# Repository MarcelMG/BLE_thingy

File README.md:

# BLEthingy
BLEthingy is a small battery-powered device with Bluetooth-Low-Energy connectivity.

The main microcontroller used is an AVR ATtiny3216 from the new tiny-1 series.

BLE connectivity is provided by a RN4871-I RF module.

There is an ADXL345 3-axis accelerometer onboard for motion detection. It sits on a GY-291 breakout-board, which is very cheap and avoids hand-soldering the tiny package of the ADXL345 which is virtually impossible without hot air / reflow oven. The GY-291 has to be slightly modified, see [here](https://github.com/MarcelMG/BLE_thingy/blob/master/hardware/GY-291_mod.md) for further instructions.

A pushbutton and a user LED are also onboard.

On the back of the PCB, a holder for a CR2032 coin cell is mounted.

An enclosure has been designed which can be 3D-printed.

(c) 2019 Marcel Meyer-Garcia
<br />This work (hardware and software) is licensed under a <a rel="license" href="http://creativecommons.org/licenses/by-nc/4.0/">Creative Commons Attribution-NonCommercial 4.0 International License</a>.

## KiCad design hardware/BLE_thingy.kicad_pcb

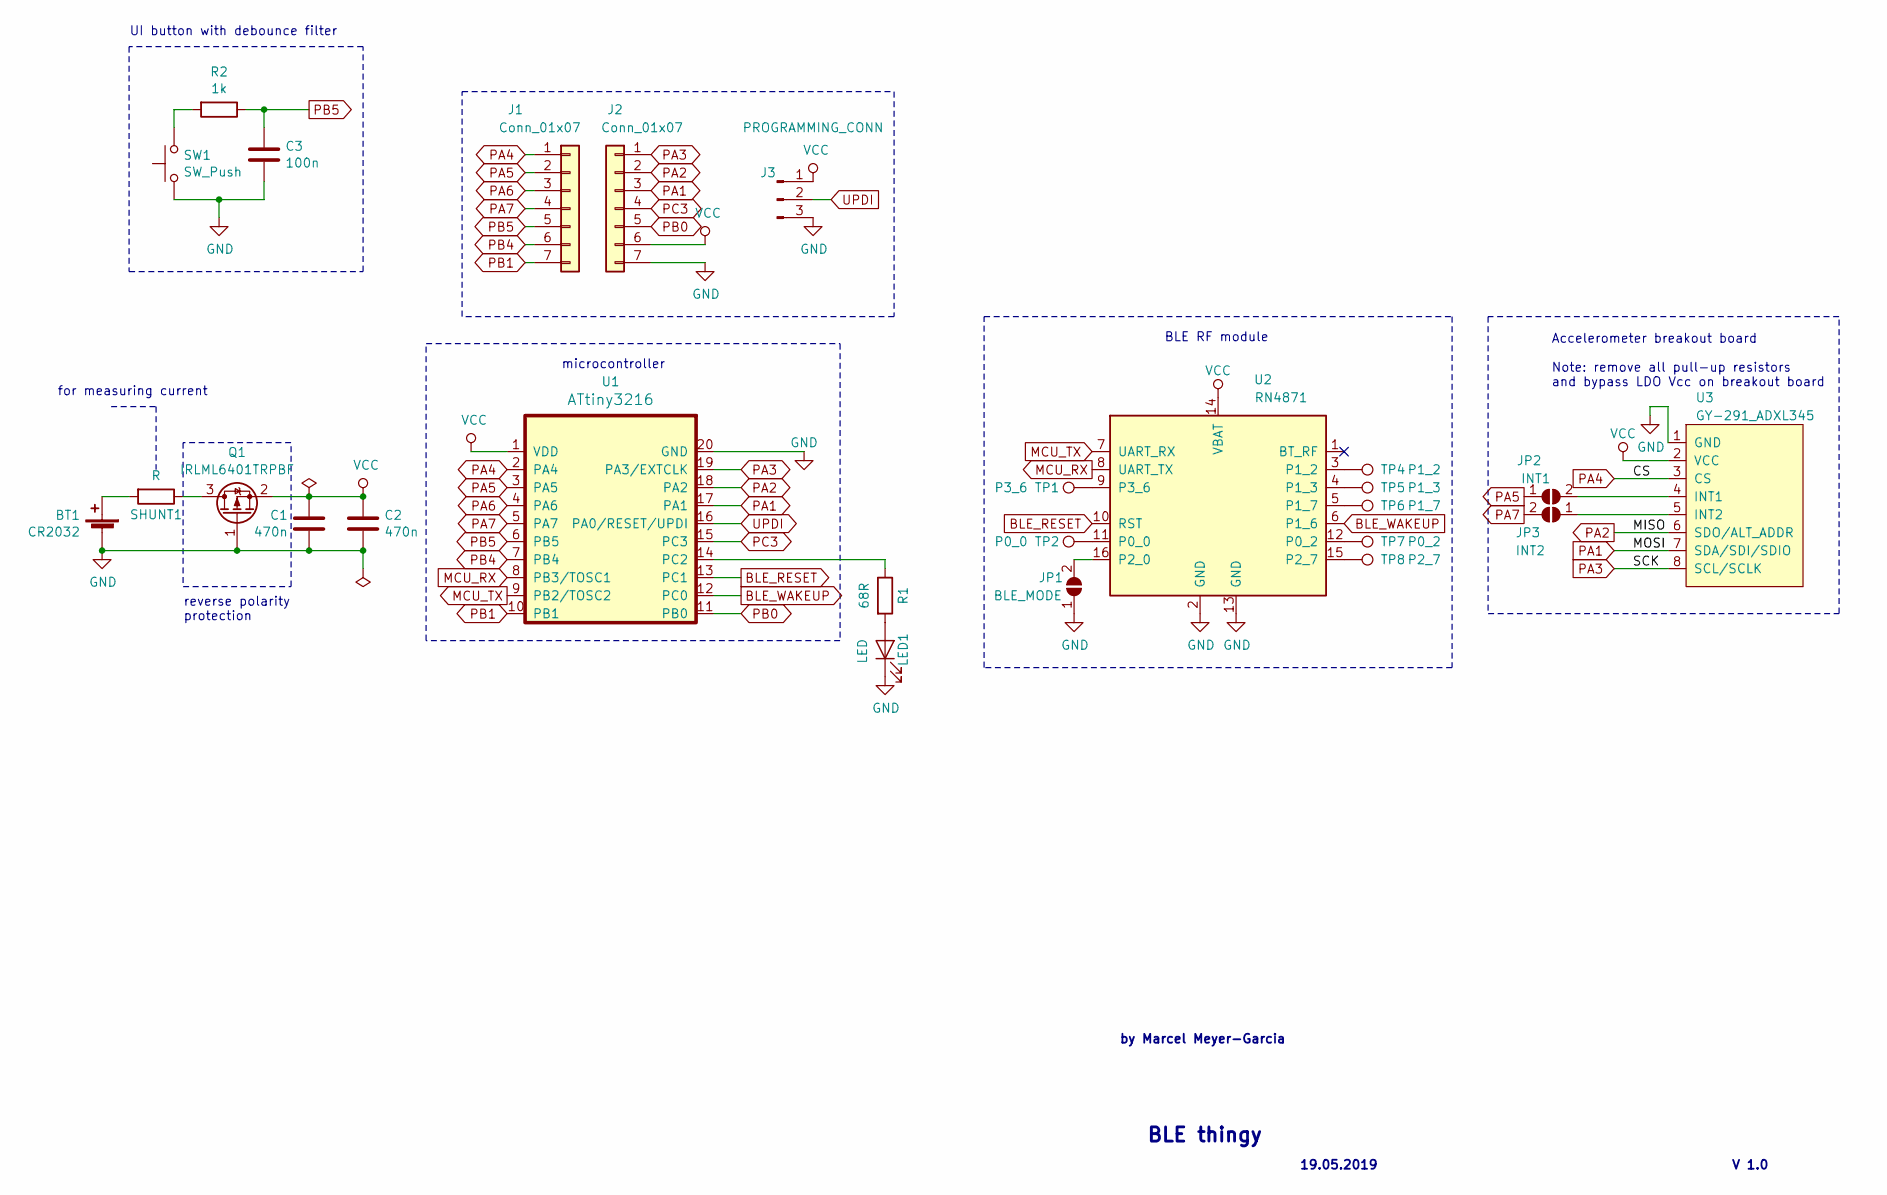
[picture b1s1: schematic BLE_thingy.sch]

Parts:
BT1: CR2032; BatteryHolder_Keystone_3034_1x20mm
C1, C2: 470n; C_0805_2012Metric_Pad1.15x1.40mm_HandSolder
C3: 100n; C_0805_2012Metric_Pad1.15x1.40mm_HandSolder
J1, J2: Conn_01x07; PinHeader_1x07_P2.54mm_Vertical
J3: PROGRAMMING_CONN; PinHeader_1x03_P2.54mm_Vertical
JP1: BLE_MODE; SolderJumper-2_P1.3mm_Open_TrianglePad1.0x1.5mm
JP2: INT1; SolderJumper-2_P1.3mm_Open_TrianglePad1.0x1.5mm
JP3: INT2; SolderJumper-2_P1.3mm_Open_TrianglePad1.0x1.5mm
LED1: LED; LED_1206_3216Metric_Pad1.42x1.75mm_HandSolder
Q1: IRLML6401TRPBF; SOT-23
R1: 68R; R_0805_2012Metric_Pad1.15x1.40mm_HandSolder
R2: 1k; R_0805_2012Metric_Pad1.15x1.40mm_HandSolder
SHUNT1: R; R_0805_2012Metric_Pad1.15x1.40mm_HandSolder
SW1: SW_Push; SW_PUSH_6mm_H4.3mm
TP1: P3_6; TestPoint_Pad_D2.0mm
TP2: P0_0; TestPoint_Pad_D2.0mm
TP4: P1_3; TestPoint_Pad_D2.0mm
TP5: P1_2; TestPoint_Pad_D2.0mm
TP6: P1_7; TestPoint_Pad_D2.0mm
TP7: P0_2; TestPoint_Pad_D2.0mm
TP8: P2_7; TestPoint_Pad_D2.0mm
U1: ATtiny3216; SOIC-20_elongated_pads
U2: RN4871; Microchip_RN4871
U3: GY-291_ADXL345; GY-291_ADXL345_breakout_board

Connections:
BLE_RESET: U1.13 (PC1), U2.10 (RST)
BLE_WAKEUP: U1.12 (PC0), U2.6 (P1_6)
GND: BT1.2 (-), C1.2, C2.2, C3.2, J2.7, J3.3, JP1.1 (A), LED1.1 (K), Q1.1 (G), SW1.1, U1.20 (GND), U2.2 (GND), U2.13 (GND), U3.1 (GND)
MCU_RX: U1.8 (PB3/TOSC1), U2.8 (UART_TX)
MCU_TX: U1.9 (PB2/TOSC2), U2.7 (UART_RX)
unnamed 5: BT1.1 (+), SHUNT1.2; also elsewhere on the board
unnamed: JP1.2 (B), U2.16 (P2_0)
unnamed: JP2.2 (B), U3.4 (INT1)
unnamed: JP3.1 (A), U3.5 (INT2)
unnamed: LED1.2 (A), R1.2
unnamed 10: Q1.3 (D), SHUNT1.1; also elsewhere on the board
unnamed: R1.1, U1.14 (PC2)
unnamed: R2.2, SW1.2
unnamed: TP1.1, U2.9 (P3_6)
unnamed: TP2.1, U2.11 (P0_0)
unnamed: TP4.1, U2.3 (P1_2)
unnamed: TP5.1, U2.4 (P1_3)
unnamed: TP6.1, U2.5 (P1_7)
unnamed: TP7.1, U2.12 (P0_2)
unnamed: TP8.1, U2.15 (P2_7)
PA1: J2.3, U1.17 (PA1), U3.7 (SDA/SDI/SDIO)
PA2: J2.2, U1.18 (PA2), U3.6 (SDO/ALT_ADDR)
PA3: J2.1, U1.19 (PA3/EXTCLK), U3.8 (SCL/SCLK)
PA4: J1.1, U1.2 (PA4), U3.3 (CS)
PA5: J1.2, JP2.1 (A), U1.3 (PA5)
PA6: J1.3, U1.4 (PA6)
PA7: J1.4, JP3.2 (B), U1.5 (PA7)
PB0: J2.5, U1.11 (PB0)
PB1: J1.7, U1.10 (PB1)
PB4: J1.6, U1.7 (PB4)
PB5: C3.1, J1.5, R2.1, U1.6 (PB5)
PC3: J2.4, U1.15 (PC3)
UPDI: J3.2, U1.16 (PA0/RESET/UPDI)
VCC: C1.1, C2.1, J2.6, J3.1, Q1.2 (S), U1.1 (VDD), U2.14 (VBAT), U3.2 (VCC)

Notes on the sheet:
Accelerometer breakout board Note: remove all pull-up resistors and bypass LDO Vcc on breakout board
for measuring current
BLE RF module
microcontroller
reverse polarity protection
UI button with debounce filter
BLE thingy
19.05.2019
V 1.0
by Marcel Meyer-Garcia

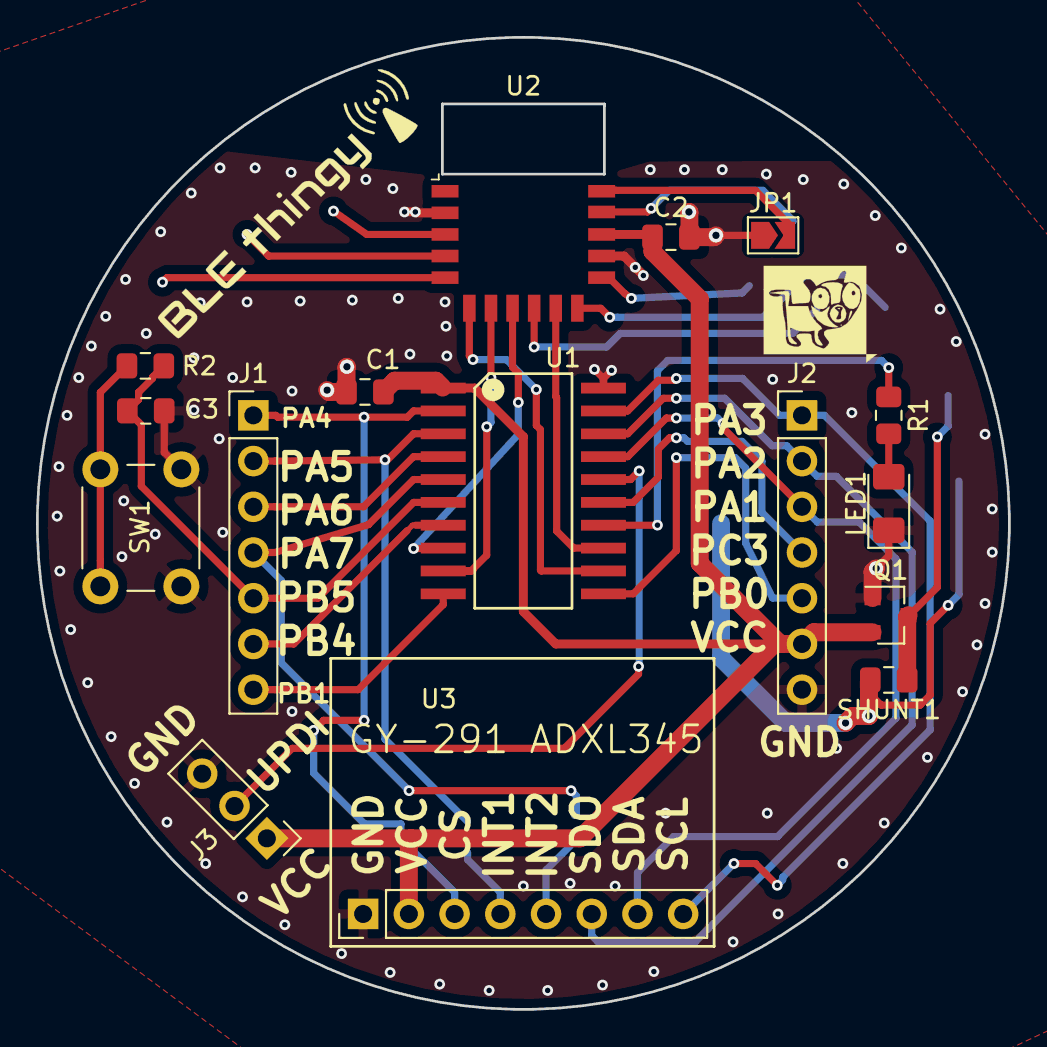
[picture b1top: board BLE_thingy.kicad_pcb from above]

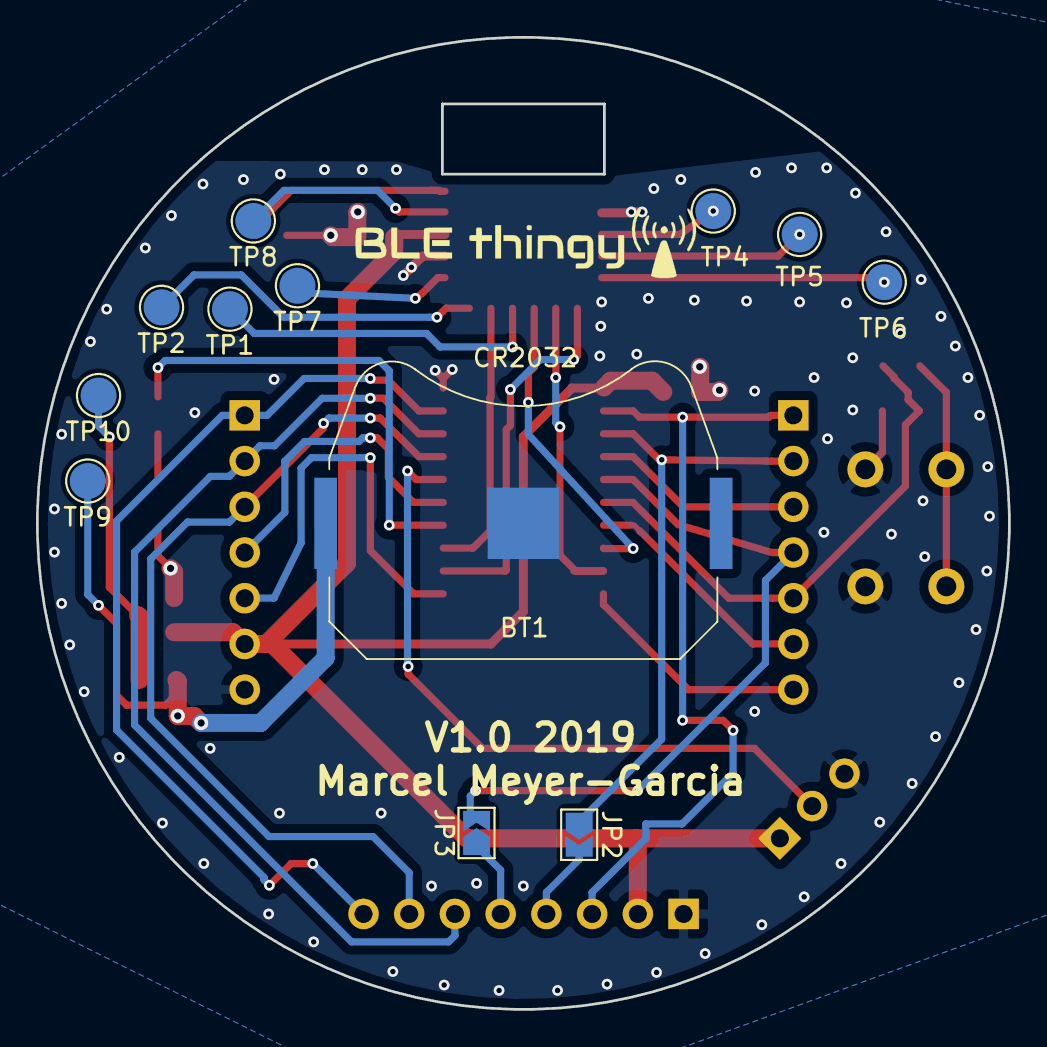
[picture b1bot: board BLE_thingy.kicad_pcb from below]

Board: 2 copper layers, 54.0 x 54.0 mm, 28 parts (12 on the bottom side), 34 nets.

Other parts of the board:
TP9: SHUNT+; TestPoint_Pad_D2.0mm
TP10: SHUNT-; TestPoint_Pad_D2.0mm

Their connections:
unnamed 5: TP9.1; also elsewhere on the board
unnamed 10: TP10.1; also elsewhere on the board

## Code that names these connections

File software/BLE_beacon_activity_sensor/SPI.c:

/*	SPI master on AVR ATtiny3216
 *	by Marcel Meyer Garcia
 *	see LICENSE.txt
*/
#include "SPI.h"

// initialize the SPI peripheral with a certain configuration stored in the SPI_config struct
void SPI_init(struct SPI_config* SPIcfg){
	SPI_CS_high();
	PORTA.DIRSET = PIN1_bm | PIN3_bm | PIN4_bm; // MOSI ,SCK and CS pins as outputs (PA1, PA3 and PA4)
	PORTA.DIRCLR = PIN2_bm;	// MISO pin (PA2) as input
	SPI0.CTRLB = SPIcfg->mode; // set SPI mode (clock polarity and phase)
	SPI0.CTRLA = SPIcfg->prescaler;
	if(SPIcfg->useDoubleSpeed == true){
		SPI0.CTRLA |= SPI_CLK2X_bm; 
	}
	if(SPIcfg->dataOrder == SPI_LSB_FIRST){
		SPI0.CTRLA |= SPI_DORD_bm; // set LSB first (MSB first is default)
	}
	SPI0.CTRLA |= SPI_ENABLE_bm | SPI_MASTER_bm;
}

// transmit and receive one byte (polling)
uint8_t SPI_transmit(uint8_t tx_data){
	    SPI0.DATA = tx_data;	// put byte to be sent in transmit buffer
	    while (!(SPI0.INTFLAGS & SPI_IF_bm));	// wait until transmit buffer is empty, i.e. transmission is finished
	    return SPI0.DATA;	// return received byte from slave
}

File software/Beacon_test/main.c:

/* iBeacon example */

#include <avr/io.h>
#define F_CPU 3333333
#include <util/delay.h>
#include <string.h>
#include "uart.h"
#include <stdio.h>
int USART0_printChar(char c, FILE *stream){
	USART0_sendChar(c);
	return 0;
}
FILE USART_stream = FDEV_SETUP_STREAM(USART0_printChar, NULL, _FDEV_SETUP_WRITE);

// use pin PB1 for UART TX
#define UART_TX_LOW() PORTB.OUTCLR=PIN1_bm
#define UART_TX_HIGH() PORTB.OUTSET=PIN1_bm
#define BAUD 9600
#define ERROR_COMP 0.00 // for clock freq. deviation error compensation, e.g. 0.05 = 5%, just try until it works :)
#define BAUD_DELAY_US 1000000UL*(1+ERROR_COMP)/BAUD
void dbg_print_char(char c){
	c = ~c;
	UART_TX_LOW();            // start bit
	for( uint8_t i = 10; i; i-- ){        // 10 bits
		_delay_us(BAUD_DELAY_US);            // bit duration
		if( c & 1 ){
			UART_TX_LOW();        // data bit 0
			}else{
			UART_TX_HIGH();           // data bit 1 or stop bit
		}
		c >>= 1;
	}
}
void dbg_print_str(char* str){
	while(*str) dbg_print_char(*str++);
}

// wait for a specific character in the RN4871's response and print the response for debugging
void RN4871_waitfor(char endchar){
	char str[10];
	char* str_ptr = str;
	*str_ptr = USART0_readChar();
	while( *str_ptr != endchar ){
		++str_ptr;
		*str_ptr = USART0_readChar();
	}
	++str_ptr;
	*str_ptr = '\0';
	dbg_print_str(str);	
}

char UUID[32] = "123456789ABCDEF123456789ABCDEF12";

void iBeacon_advertise(uint16_t minor, uint16_t major, uint8_t TxPower){
	printf("IB,Z\r"); // clear advertisement content
	RN4871_waitfor('K'); // wait for "AOK" response
	printf("IB,FF,"); // set custom manufacturer (FF) advertisement content
	printf("4C000215"); // iBeacon preamble
	printf(UUID); // device UUID
	printf("%.4X", minor); // minor (2 bytes, i.e. uint16_t)
	printf("%.4X", major); // major (2 bytes, i.e. uint16_t)
	printf("%.2X", TxPower); // TxPower (1 byte, i.e. uint8_t) calibration value for distance calculation
	putchar('\r'); // end "IB,FF,..." command with carriage return 
	RN4871_waitfor('K'); // wait for "AOK" response
}

int main(void)
{
	PORTB.DIRSET = PIN1_bm;	// TX-pin PB1 as output for debugging
	PORTC.DIRSET = PIN2_bm;	// pin PC2 (LED) as output
	PORTC.OUTCLR = PIN2_bm; // LED off

	PORTC.DIRSET = PIN0_bm; // PC0 - BLEwakeup as output
	PORTC.OUTCLR = PIN0_bm; // BLE uart active
	
	USART0_init(); // init UART to talk to RN4871
	stdout = &USART_stream; // redirect stdout to UART
	
	/* reset RN4871 */
	PORTC.OUTSET = PIN1_bm; // BLE RESET HIGH
	PORTC.DIRSET = PIN1_bm; // pin PC1 (BLE RESET) as output
	PORTC.OUTCLR = PIN1_bm;
	_delay_ms(10);
	PORTC.OUTSET = PIN1_bm;
	
	_delay_ms(100); // wait for RN4871 to boot up and be ready
	dbg_print_str("start\n");
	
	printf("$$$"); // enter command mode
	RN4871_waitfor('>'); // get response, should be: "CMD>"
	_delay_ms(1);
	printf("SS,10\r"); // set service to non-connectable beacon
	RN4871_waitfor('K'); // get response, should be: "AOK"
	_delay_ms(1);
	printf("STB,0640\r"); // set advertisement interval to 640*0.625ms = 1s
	RN4871_waitfor('K'); // get response, should be: "AOK"
	_delay_ms(1);
	printf("SO,1\r"); // enable low power mode
	RN4871_waitfor('K'); // get response, should be: "AOK"
	
	PORTC.OUTSET = PIN0_bm; // put RN4871 in sleep mode
	
	while (1){	
		for(uint16_t i=0; i<65536; ++i){
			PORTC.OUTCLR = PIN0_bm; // wake up RN4871
			_delay_ms(5); // RN4871 needs 5ms to wake up until UART is responsive
			iBeacon_advertise(i, 0xFFFF-i, 100); // advertise as iBeacon
			PORTC.OUTSET = PIN0_bm; // put RN4871 in sleep mode
			PORTC.OUTTGL = PIN2_bm; // LED toggle
			_delay_ms(1000);
			
		}
	}
	return 0;
}

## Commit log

2019-05-19 Update LICENSE
2019-06-15 initial upload
2019-06-15 added some more comments
2019-06-21 Rename README.md.txt to README.md
2019-06-22 added pushbutton and changed advertisement interval
    added pushbutton support and changed advertisement interval to 4s
2019-06-22 changed RTC wakeup interval and BLE Adv. interval, +LED flash
2019-06-22 changed intervals
2019-06-27 updated schematic
